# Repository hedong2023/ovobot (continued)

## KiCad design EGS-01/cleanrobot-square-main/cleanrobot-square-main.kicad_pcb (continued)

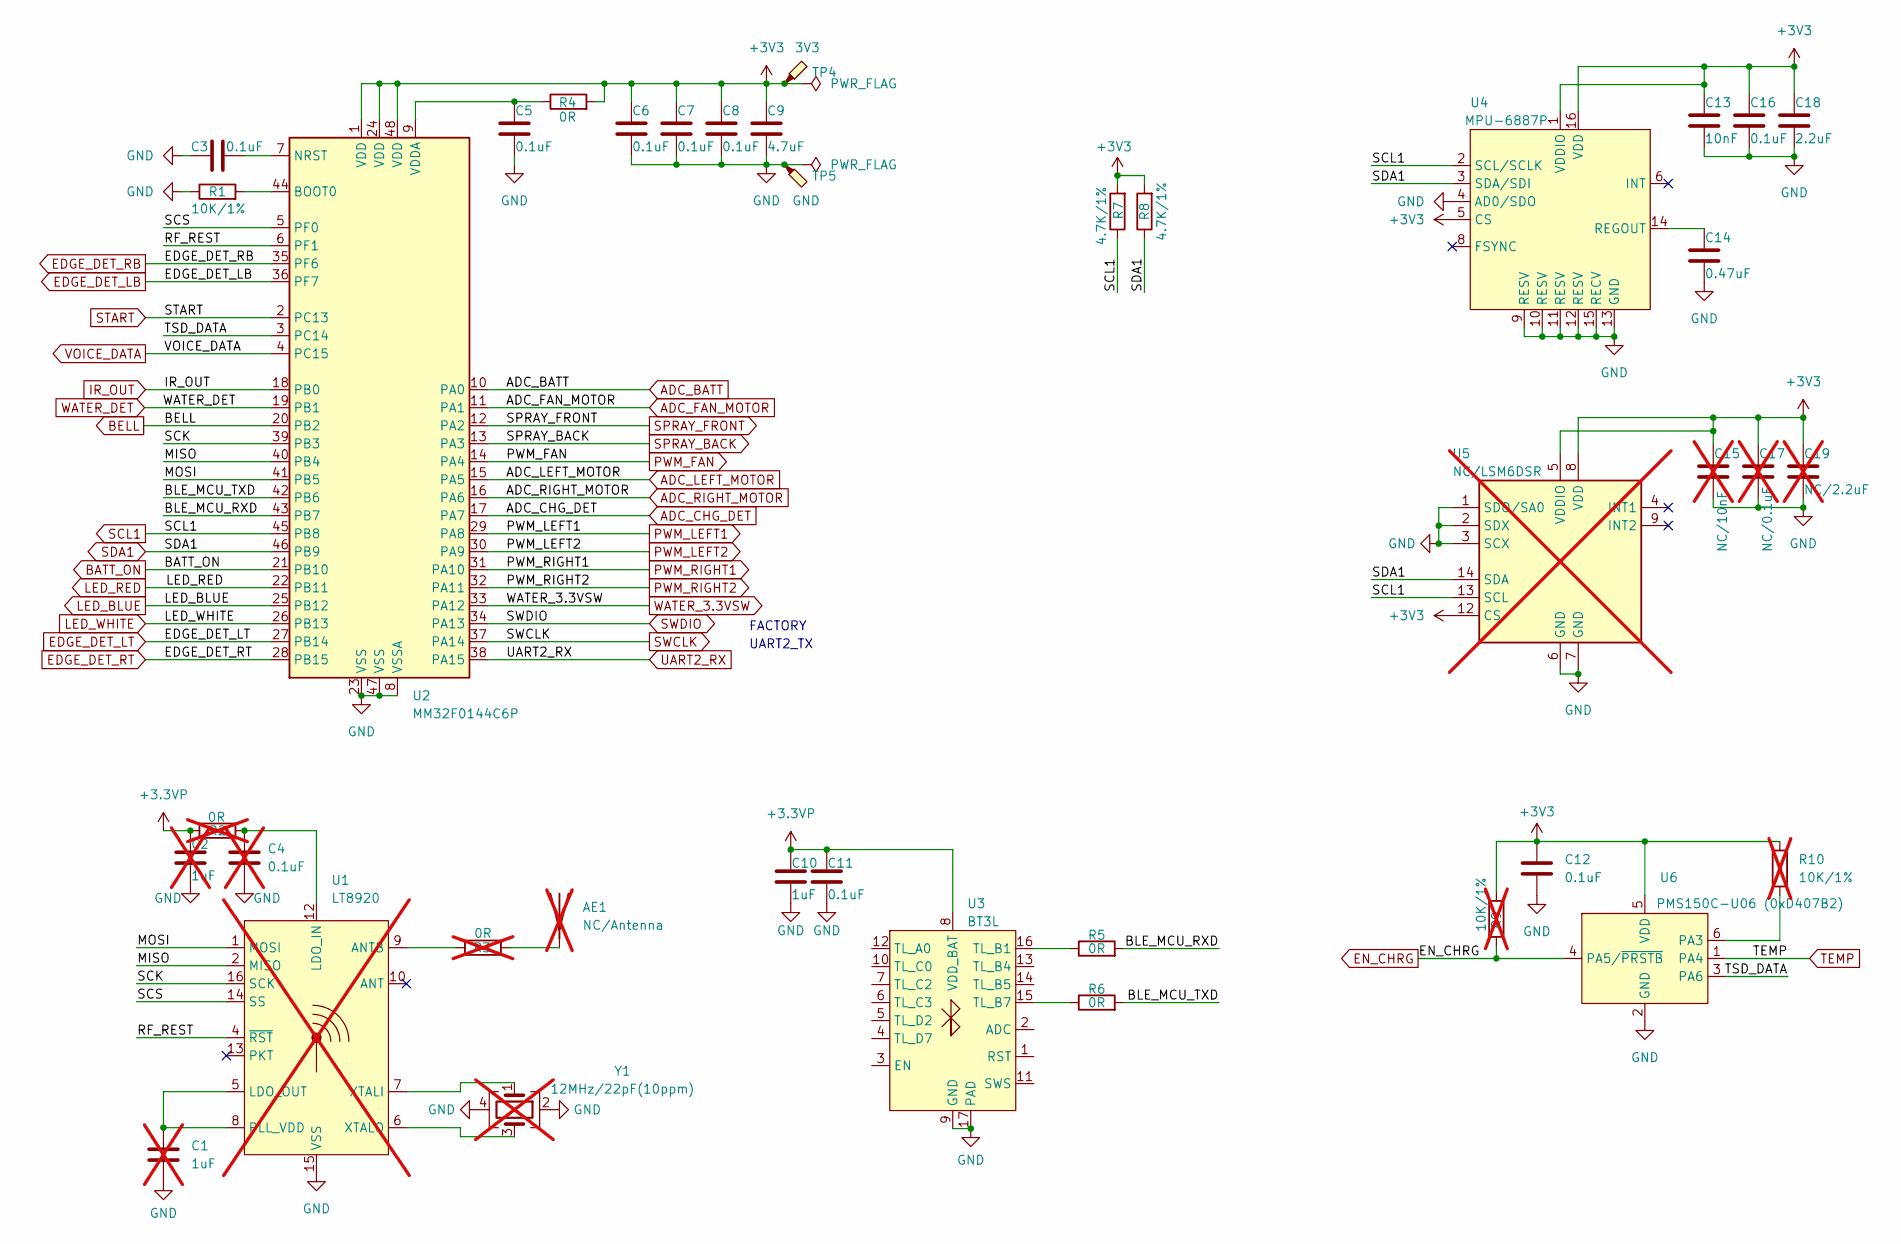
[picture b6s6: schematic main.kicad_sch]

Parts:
AE1: NC/Antenna; Ovo_PA2401_2.4GHz_Right; not fitted
C1, C2: 1uF; C_0603_1608Metric; not fitted
C3, C5, C6, C7, C8, C11, C12, C16: 0.1uF; C_0603_1608Metric
C4: 0.1uF; C_0603_1608Metric; not fitted
C9: 4.7uF; C_0603_1608Metric
C10: 1uF; C_0603_1608Metric
C13: 10nF; C_0603_1608Metric
C14: 0.47uF; C_0603_1608Metric
C15: NC/10nF; C_0603_1608Metric; not fitted
C17: NC/0.1uF; C_0603_1608Metric; not fitted
C18: 2.2uF; C_0603_1608Metric
C19: NC/2.2uF; C_0603_1608Metric; not fitted
R1: 10K/1%; R_0603_1608Metric
R2, R3: 0R; R_0603_1608Metric; not fitted
R4, R5, R6: 0R; R_0603_1608Metric
R7, R8: 4.7K/1%; R_0603_1608Metric
R9, R10: 10K/1%; R_0603_1608Metric; not fitted
TP4: 3V3; TestPoint_Pad_D1.0mm
TP5: GND; TestPoint_Pad_D1.0mm
U1: LT8920; TSSOP-16_4.4x5mm_P0.65mm; not fitted
U2: MM32F0144C6P; LQFP-48_7x7mm_P0.5mm
U3: BT3L; Tuya_BT3L
U4: MPU-6887P; LGA-16_3x3mm_P0.5mm_LayoutBorder3x5y
U5: NC/LSM6DSR; LGA-14_3x2.5mm_P0.5mm_LayoutBorder3x4y; not fitted
U6: PMS150C-U06 (0xD407B2); SOT-23-6
Y1: 12MHz/22pF(10ppm); Oscillator_SMD_Abracon_ASE-4Pin_3.2x2.5mm; not fitted

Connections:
+3.3VP: C2.1, C10.1, C11.1, R2.1, U3.8 (VDD_BAT); also elsewhere on the board
+3V3: C6.2, C7.2, C8.2, C9.2, C12.1, C13.2, C15.2, C16.2, C17.2, C18.2, C19.2, R4.2, R7.2, R8.2, R9.1, R10.1, TP4.1, U2.1 (VDD), U2.24 (VDD), U2.48 (VDD), U4.1 (VDDIO), U4.5 (CS), U4.16 (VDD), U5.5 (VDDIO), U5.8 (VDD), U5.12 (CS), U6.5 (VDD); also elsewhere on the board
/main/BLE_MCU_RXD: R5.2, U2.43 (PB7)
/main/BLE_MCU_TXD: R6.2, U2.42 (PB6)
/main/MISO: U1.2 (MISO), U2.40 (PB4)
/main/MOSI: U1.1 (MOSI), U2.41 (PB5)
/main/RF_REST: U1.4 (~RST), U2.6 (PF1)
/main/SCK: U1.16 (SCK), U2.39 (PB3)
/main/SCS: U1.14 (SS), U2.5 (PF0)
/main/TSD_DATA: U2.3 (PC14), U6.3 (PA6)
ADC_BATT: U2.10 (PA0); also elsewhere on the board
ADC_CHG_DET: U2.17 (PA7); also elsewhere on the board
ADC_FAN_MOTOR: U2.11 (PA1); also elsewhere on the board
ADC_LEFT_MOTOR: U2.15 (PA5); also elsewhere on the board
ADC_RIGHT_MOTOR: U2.16 (PA6); also elsewhere on the board
BATT_ON: U2.21 (PB10); also elsewhere on the board
BELL: U2.20 (PB2); also elsewhere on the board
EDGE_DET_LB: U2.36 (PF7); also elsewhere on the board
EDGE_DET_LT: U2.27 (PB14); also elsewhere on the board
EDGE_DET_RB: U2.35 (PF6); also elsewhere on the board
EDGE_DET_RT: U2.28 (PB15); also elsewhere on the board
EN_CHRG: R9.2, U6.4 (PA5/~PRSTB); also elsewhere on the board
GND: C1.2, C2.2, C3.1, C4.2, C5.1, C6.1, C7.1, C8.1, C9.1, C10.2, C11.2, C12.2, C13.1, C14.1, C15.1, C16.1, C17.1, C18.1, C19.1, R1.1, TP5.1, U1.15 (VSS), U2.8 (VSSA), U2.23 (VSS), U2.47 (VSS), U3.9 (GND), U3.17 (PAD), U4.4 (AD0/SDO), U4.9 (RESV), U4.10 (RESV), U4.11 (RESV), U4.12 (RESV), U4.13 (GND), U4.15 (RECV), U5.1 (SDO/SA0), U5.2 (SDX), U5.3 (SCX), U5.6 (GND), U5.7 (GND), U6.2 (GND), Y1.2, Y1.4; also elsewhere on the board
IR_OUT: U2.18 (PB0); also elsewhere on the board
LED_BLUE: U2.25 (PB12); also elsewhere on the board
LED_RED: U2.22 (PB11); also elsewhere on the board
LED_WHITE: U2.26 (PB13); also elsewhere on the board
unnamed: AE1.1 (A), R3.2
unnamed: R3.1, U1.9 (ANTB)
unnamed: C4.1, R2.2, U1.12 (LDO_IN)
unnamed: C1.1, U1.5 (LDO_OUT), U1.8 (PLL_VDD)
unnamed: U1.7 (XTALI), Y1.1
unnamed: U1.6 (XTALO), Y1.3
unnamed: R1.2, U2.44 (BOOT0)
unnamed: C3.2, U2.7 (NRST)
unnamed: C5.2, R4.1, U2.9 (VDDA)
unnamed: R5.1, U3.16 (TL_B1)
unnamed: R6.1, U3.15 (TL_B7)
unnamed: C14.2, U4.14 (REGOUT)
unnamed: R10.2, U6.6 (PA3)
PWM_FAN: U2.14 (PA4); also elsewhere on the board
PWM_LEFT1: U2.29 (PA8); also elsewhere on the board
PWM_LEFT2: U2.30 (PA9); also elsewhere on the board
PWM_RIGHT1: U2.31 (PA10); also elsewhere on the board
PWM_RIGHT2: U2.32 (PA11); also elsewhere on the board
SCL1: R7.1, U2.45 (PB8), U4.2 (SCL/SCLK), U5.13 (SCL); also elsewhere on the board
SDA1: R8.1, U2.46 (PB9), U4.3 (SDA/SDI), U5.14 (SDA); also elsewhere on the board
SPRAY_BACK: U2.13 (PA3); also elsewhere on the board
SPRAY_FRONT: U2.12 (PA2); also elsewhere on the board
START: U2.2 (PC13); also elsewhere on the board
SWCLK: U2.37 (PA14); also elsewhere on the board
SWDIO: U2.34 (PA13); also elsewhere on the board
TEMP: U6.1 (PA4); also elsewhere on the board
UART2_RX: U2.38 (PA15); also elsewhere on the board
VOICE_DATA: U2.4 (PC15); also elsewhere on the board
WATER_3.3VSW: U2.33 (PA12); also elsewhere on the board
WATER_DET: U2.19 (PB1); also elsewhere on the board

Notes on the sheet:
UART2_TX
FACTORY

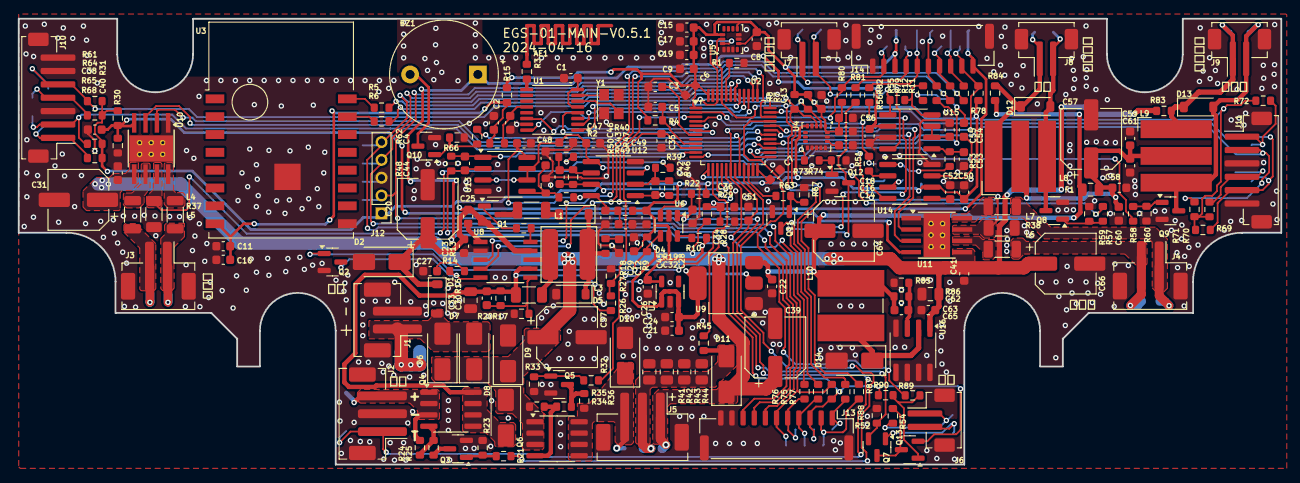
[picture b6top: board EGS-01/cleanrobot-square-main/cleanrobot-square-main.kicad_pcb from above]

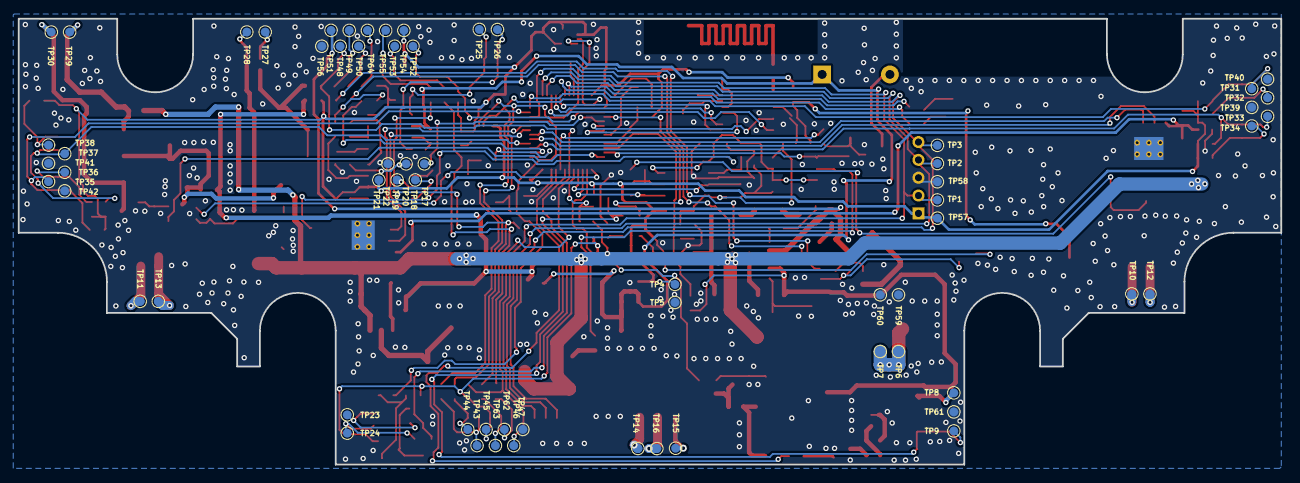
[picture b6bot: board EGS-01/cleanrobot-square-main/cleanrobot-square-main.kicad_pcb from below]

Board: 2 copper layers, 141.6 x 50.0 mm, 289 parts (64 on the bottom side), 146 nets.

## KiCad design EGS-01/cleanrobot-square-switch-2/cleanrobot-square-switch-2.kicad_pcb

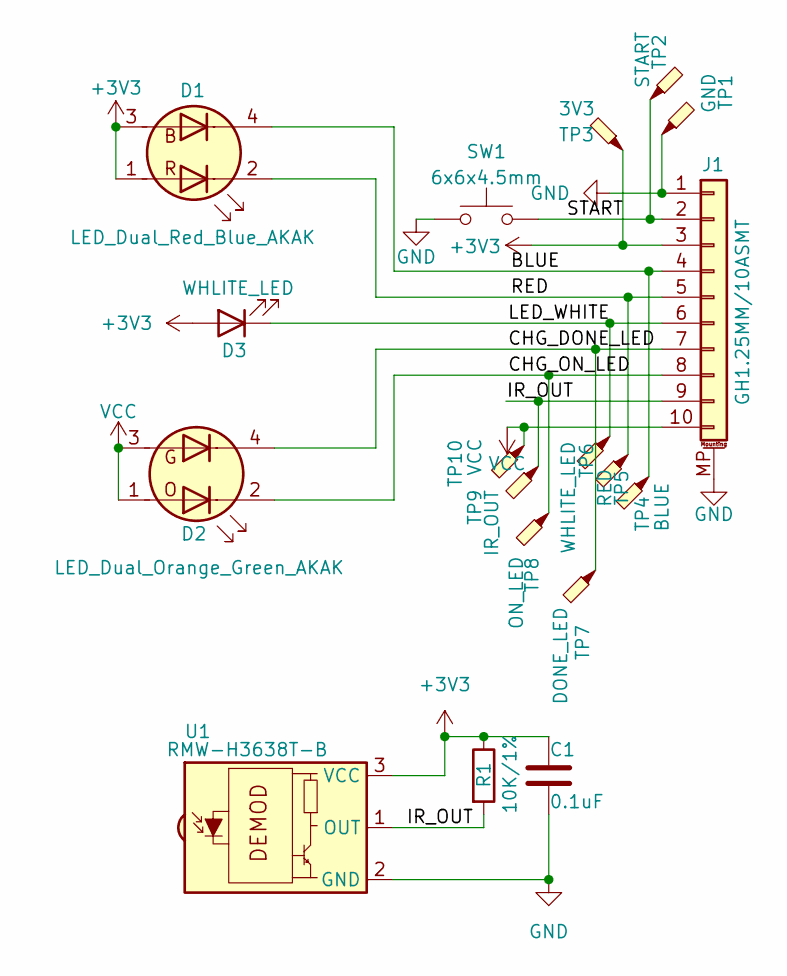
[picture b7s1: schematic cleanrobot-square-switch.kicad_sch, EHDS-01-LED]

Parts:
C1: 0.1uF; C_0603_1608Metric
D1: LED_Dual_Red_Blue_AKAK; LED_Dual_1.6x1.5mm
D2: LED_Dual_Orange_Green_AKAK; LED_Dual_1.6x1.5mm
D3: WHLITE_LED; LED_0603_1608Metric
J1: GH1.25MM/10ASMT; JST_GH_BM10B-GHS-TBT_1x10-1MP_P1.25mm_Vertical
R1: 10K/1%; R_0603_1608Metric
SW1: 6x6x4.5mm; SW_Push_1P1T_NO_6x6mm_H4.5mm
TP1: GND; TestPoint_Pad_D1.0mm
TP2: START; TestPoint_Pad_D1.0mm
TP3: 3V3; TestPoint_Pad_D1.0mm
TP4: BLUE; TestPoint_Pad_D1.0mm
TP5: RED; TestPoint_Pad_D1.0mm
TP6: WHLITE_LED; TestPoint_Pad_D1.0mm
TP7: DONE_LED; TestPoint_Pad_D1.0mm
TP8: ON_LED; TestPoint_Pad_D1.0mm
TP9: IR_OUT; TestPoint_Pad_D1.0mm
TP10: VCC; TestPoint_Pad_D1.0mm
U1: RMW-H3638T-B; Everlight_IRM-3640CF45

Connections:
+3V3: C1.1, D1.1 (A1), D1.3 (A2), D3.2 (A), J1.3, R1.1, TP3.1, U1.3 (VCC)
/BLUE: D1.4 (K2), J1.4, TP4.1
/CHG_DONE_LED: D2.4 (K2), J1.7, TP7.1
/CHG_ON_LED: D2.2 (K1), J1.8, TP8.1
/IR_OUT: J1.9, R1.2, TP9.1, U1.1 (OUT)
/LED_WHITE: D3.1 (K), J1.6, TP6.1
/RED: D1.2 (K1), J1.5, TP5.1
/START: J1.2, SW1.2, TP2.1
GND: C1.2, J1.1, J1.MP (MountPin), SW1.1, TP1.1, U1.2 (GND)
VCC: D2.1 (A1), D2.3 (A2), J1.10, TP10.1

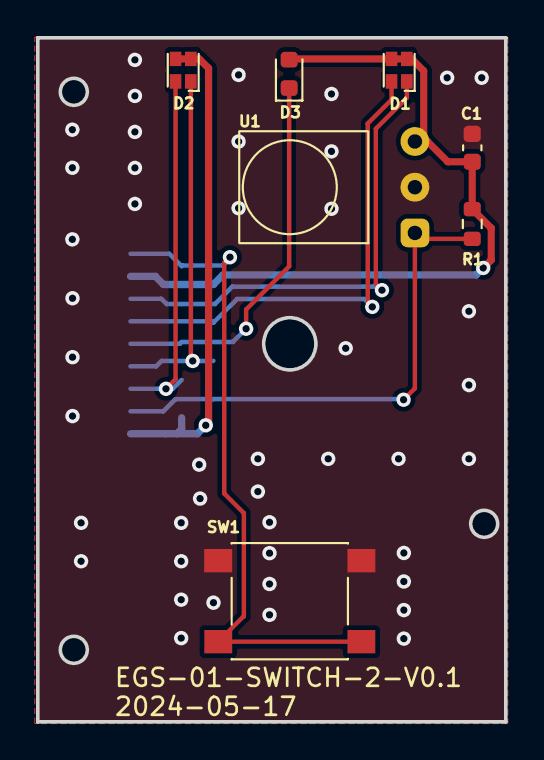
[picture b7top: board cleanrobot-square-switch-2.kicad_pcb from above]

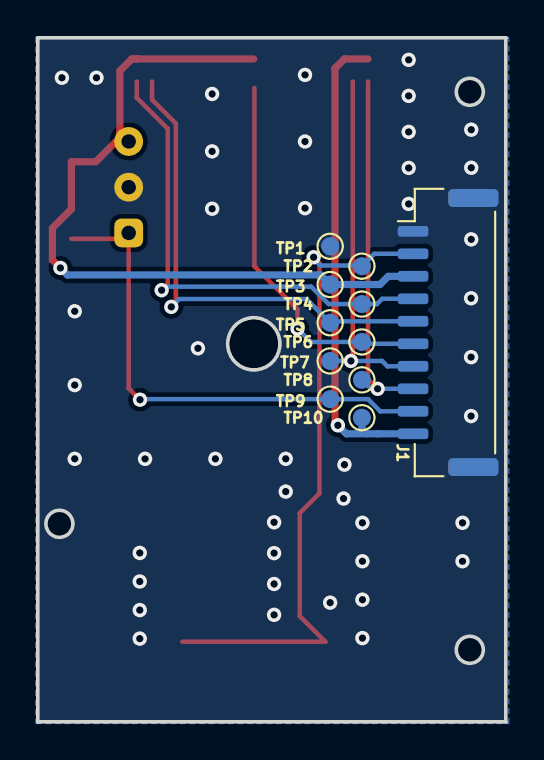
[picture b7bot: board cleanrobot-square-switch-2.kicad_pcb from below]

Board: 2 copper layers, 26.0 x 38.0 mm, 18 parts (11 on the bottom side), 10 nets.
